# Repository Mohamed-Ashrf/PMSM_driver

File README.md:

# PMSM_driver
micro-controller based driver for PMSM and BLDC motors
# PMSM_driver
micro-controller based driver for PMSM and BLDC motors

# main components 
  1- STM32f446RE as main micro controller.
  2- DRV8323H as the moset driver and integrated curent sensor.
  3- CSD19534Q5A, a 100V rated mosfets.
  
# main functions
this driver is mainly a three phase inverter, so it can be used to drive ay three phase machie within the range of 60V or less (maily for 48V systems), it also can be used as an H-bridge by utilizig onlt two phases, the main PCB has an interface for encoder to be used in acuators, the driver also provides 12V 1.5A output.

# BETA
the hardware is still under testig so soon the main version will be uploaded plus the code for interfacing with the driver, mainly Six-step commutation ad FOC will be implemented.

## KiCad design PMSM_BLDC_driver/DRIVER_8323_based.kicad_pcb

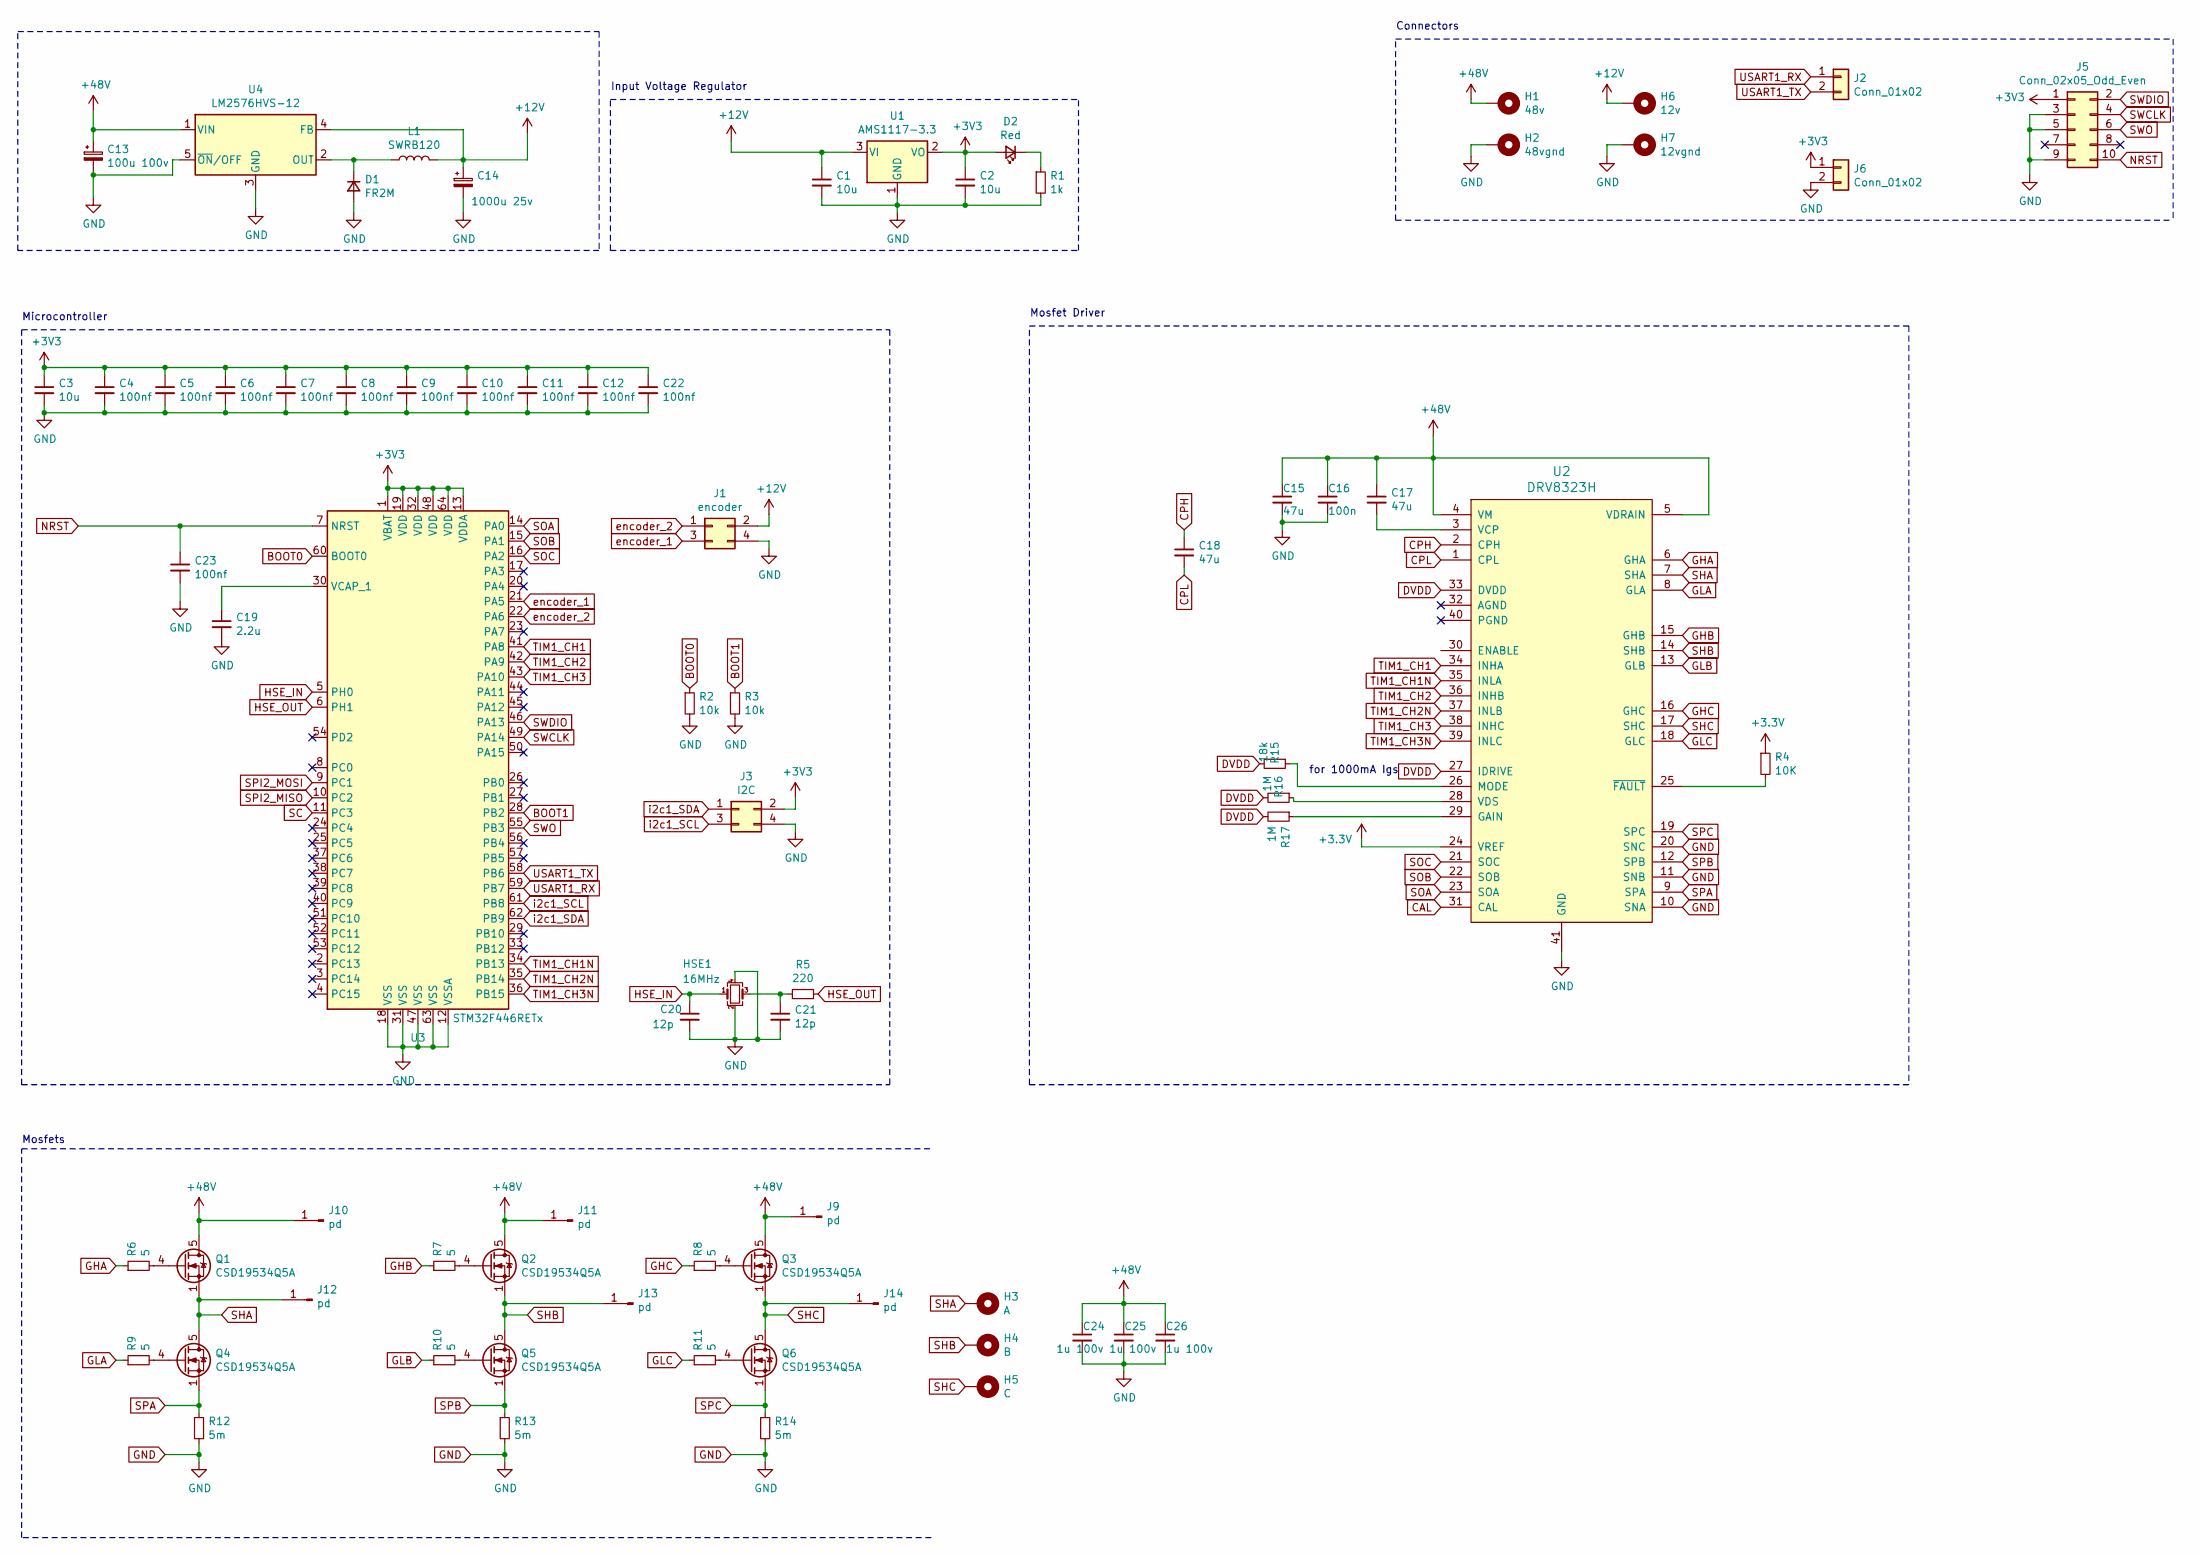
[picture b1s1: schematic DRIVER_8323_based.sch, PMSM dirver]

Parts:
C1, C2: 10u; C_0805_2012Metric
C3: 10u; C_0603_1608Metric
C4, C5, C6, C7, C8, C9, C10, C11, C12, C22, C23: 100nf; C_0402_1005Metric
C13: 100u 100v; CP_Elec_10x10
C14: 1000u 25v; CP_Elec_10x10
C15, C17, C18: 47u; C_0603_1608Metric
C16: 100n; C_0603_1608Metric
C19: 2.2u; C_0603_1608Metric
C20, C21: 12p; C_0402_1005Metric
C24, C25, C26: 1u 100v; C_1206_3216Metric
D1: FR2M; D_SMB
D2: Red; LED_0603_1608Metric
H1: 48v; MountingHole_2.7mm_Pad
H2: 48vgnd; MountingHole_2.7mm_Pad
H3: A; MountingHole_2.7mm_Pad
H4: B; MountingHole_2.7mm_Pad
H5: C; MountingHole_2.7mm_Pad
H6: 12v; MountingHole_2.2mm_M2_DIN965_Pad
H7: 12vgnd; MountingHole_2.2mm_M2_DIN965_Pad
HSE1: 16MHz; Crystal_SMD_3225-4Pin_3.2x2.5mm
J1: encoder; PinHeader_2x02_P2.54mm_Horizontal
J2, J6: Conn_01x02; PinHeader_1x02_P2.54mm_Horizontal
J3: I2C; PinHeader_2x02_P2.54mm_Horizontal
J5: Conn_02x05_Odd_Even; PinHeader_2x05_P2.54mm_Vertical
J9, J10, J11, J12, J13, J14: pd; SolderWirePad_1x01_SMD_1x2mm
L1: SWRB120; L_12x12mm_H4.5mm
Q1, Q2, Q3, Q4, Q5, Q6: CSD19534Q5A; TDSON-8-1
R1: 1k; R_0603_1608Metric
R2, R3: 10k; R_0805_2012Metric
R4: 10K; R_0603_1608Metric
R5: 220; R_0603_1608Metric
R6, R7, R8, R9, R10, R11: 5; R_0805_2012Metric
R12, R13, R14: 5m; R_2512_6332Metric
R15: 18k; R_0603_1608Metric
R16, R17: 1M; R_0603_1608Metric
U1: AMS1117-3.3; SOT-223-3_TabPin2
U2: DRV8323H; QFN-40-1EP_6x6mm_P0.5mm_EP4.6x4.6mm_ThermalVias
U3: STM32F446RETx; LQFP-64_10x10mm_P0.5mm
U4: LM2576HVS-12; TO-263-5_TabPin3

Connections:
+12V: C1.1, C14.1, H6.1, J1.2, L1.2, U1.3 (VI), U4.4 (FB)
+48V: C13.1, C15.1, C16.1, C17.1, C24.1, C25.1, C26.1, H1.1, J9.1, J10.1, J11.1, Q1.5 (D), Q2.5 (D), Q3.5 (D), U2.4 (VM), U2.5 (VDRAIN), U4.1 (VIN)
BOOT0: R2.1, U3.60 (BOOT0)
BOOT1: R3.1, U3.28 (PB2)
CAL: U2.31 (CAL)
CPH: C18.1, U2.2 (CPH)
CPL: C18.2, U2.1 (CPL)
DVDD: R15.2, R16.2, R17.2, U2.27 (IDRIVE), U2.33 (DVDD)
GHA: R6.1, U2.6 (GHA)
GHB: R7.1, U2.15 (GHB)
GHC: R8.1, U2.16 (GHC)
GLA: R9.1, U2.8 (GLA)
GLB: R10.1, U2.13 (GLB)
GLC: R11.1, U2.18 (GLC)
GND: C1.2, C2.2, C3.2, C4.2, C5.2, C6.2, C7.2, C8.2, C9.2, C10.2, C11.2, C12.2, C13.2, C14.2, C15.2, C16.2, C19.2, C20.2, C21.2, C22.2, C23.2, C24.2, C25.2, C26.2, D1.2 (A), H2.1, H7.1, HSE1.2, HSE1.4, J1.4, J3.4, J5.3, J5.5, J5.9, J6.2, R1.2, R2.2, R3.2, R12.2, R13.2, R14.2, U1.1 (GND), U2.10 (SNA), U2.11 (SNB), U2.20 (SNC), U2.41 (GND), U3.12 (VSSA), U3.18 (VSS), U3.31 (VSS), U3.47 (VSS), U3.63 (VSS), U4.3 (GND), U4.5 (~ON~/OFF)
HSE_IN: C20.1, HSE1.1, U3.5 (PH0)
HSE_OUT: R5.1, U3.6 (PH1)
NRST: C23.1, J5.10, U3.7 (NRST)
unnamed: C17.2, U2.3 (VCP)
unnamed: C19.1, U3.30 (VCAP_1)
unnamed: C21.1, HSE1.3, R5.2
unnamed: D1.1 (K), L1.1, U4.2 (OUT)
unnamed: D2.1 (K), R1.1
unnamed: Q1.4 (G), R6.2
unnamed: Q2.4 (G), R7.2
unnamed: Q3.4 (G), R8.2
unnamed: Q4.4 (G), R9.2
unnamed: Q5.4 (G), R10.2
unnamed: Q6.4 (G), R11.2
unnamed: R4.2, U2.25 (~FAULT)
unnamed: R15.1, U2.26 (MODE)
unnamed: R16.1, U2.28 (VDS)
unnamed: R17.1, U2.29 (GAIN)
SC: U3.11 (PC3)
SHA: H3.1, J12.1, Q1.1 (S), Q1.2 (S), Q1.3 (S), Q4.5 (D), U2.7 (SHA)
SHB: H4.1, J13.1, Q2.1 (S), Q2.2 (S), Q2.3 (S), Q5.5 (D), U2.14 (SHB)
SHC: H5.1, J14.1, Q3.1 (S), Q3.2 (S), Q3.3 (S), Q6.5 (D), U2.17 (SHC)
SOA: U2.23 (SOA), U3.14 (PA0)
SOB: U2.22 (SOB), U3.15 (PA1)
SOC: U2.21 (SOC), U3.16 (PA2)
SPA: Q4.1 (S), Q4.2 (S), Q4.3 (S), R12.1, U2.9 (SPA)
SPB: Q5.1 (S), Q5.2 (S), Q5.3 (S), R13.1, U2.12 (SPB)
SPC: Q6.1 (S), Q6.2 (S), Q6.3 (S), R14.1, U2.19 (SPC)
SPI2_MISO: U3.10 (PC2)
SPI2_MOSI: U3.9 (PC1)
SWCLK: J5.4, U3.49 (PA14)
SWDIO: J5.2, U3.46 (PA13)
SWO: J5.6, U3.55 (PB3)
TIM1_CH1: U2.34 (INHA), U3.41 (PA8)
TIM1_CH1N: U2.35 (INLA), U3.34 (PB13)
TIM1_CH2: U2.36 (INHB), U3.42 (PA9)
TIM1_CH2N: U2.37 (INLB), U3.35 (PB14)
TIM1_CH3: U2.38 (INHC), U3.43 (PA10)
TIM1_CH3N: U2.39 (INLC), U3.36 (PB15)
USART1_RX: J2.1, U3.59 (PB7)
USART1_TX: J2.2, U3.58 (PB6)
encoder_1: J1.3, U3.21 (PA5)
encoder_2: J1.1, U3.22 (PA6)
i2c1_SCL: J3.3, U3.61 (PB8)
i2c1_SDA: J3.1, U3.62 (PB9)

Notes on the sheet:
Input Voltage Regulator
Microcontroller
Connectors
Mosfet Driver
for 1000mA Igs
Mosfets

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
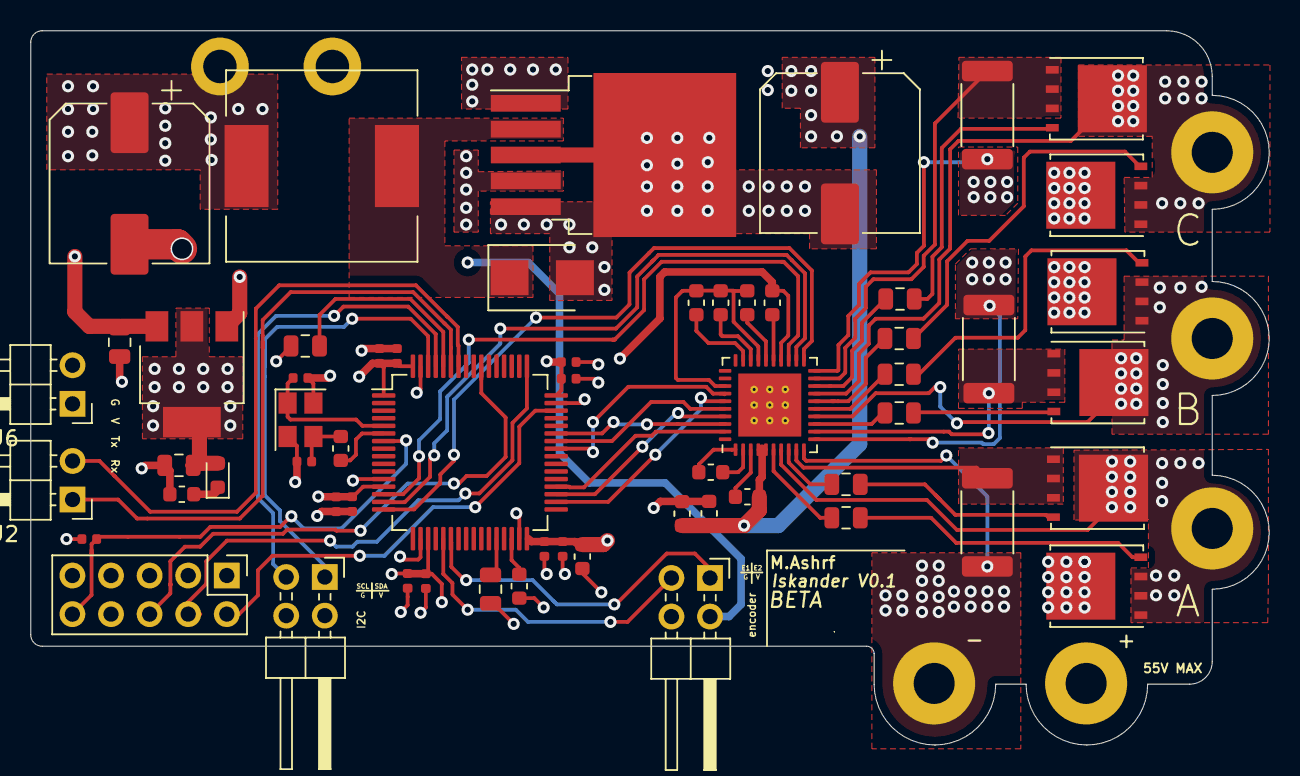
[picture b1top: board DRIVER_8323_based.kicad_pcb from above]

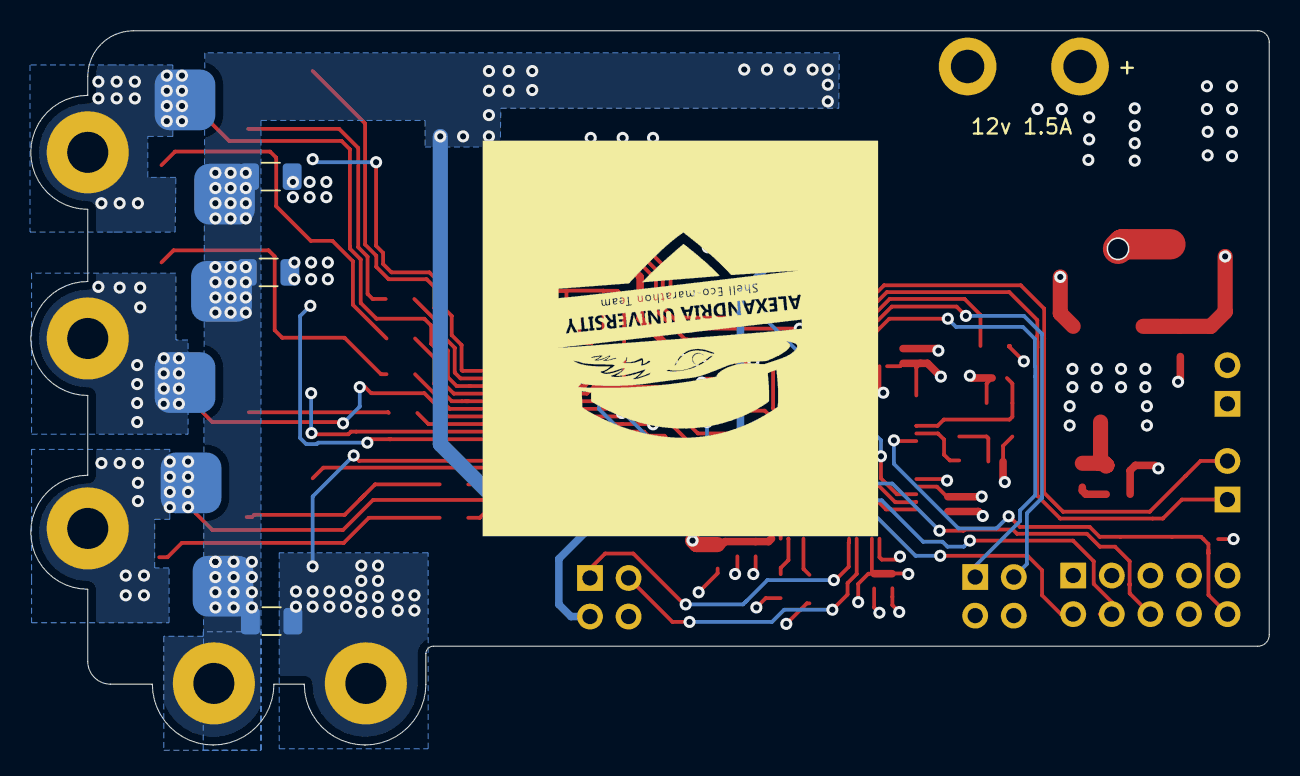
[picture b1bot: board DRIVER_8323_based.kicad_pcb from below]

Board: 4 copper layers, 81.5 x 47.0 mm, 75 parts (11 on the bottom side), 57 nets.
